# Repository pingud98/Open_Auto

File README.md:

# Open_Auto

Open Auto is an open hardware car sharing hardware platform designed for use by local car-sharing co-operatives and community associations. It originally started out as a Pi Hat, but has now changed into a standalone IOT device based on communications hardware from Particle.

The functionality is simple:
1) GPS tracking, allowing the car to be located at all times and used to update the onboard Real-time Clock (RTC)
2) RFID card access (125kHz or other frequency, requires an external module), with either CAN-bus or relays to open/close the car doors
3) Accelerometer to check driving style (requires an Electron)
4) RTC to allow for power saving (wake up once per minute to check status instead of continuously being on)
5) CAN bus interface for automotive communication
6) Particle Electron/Photon socket for Wi-Fi and/or Cellular connectivity
7) An SD card slot for data logging.
8) An I2C header for whatever else you want to connect.

We're currently working on a software stack for the Electron/Photon that will allow all the basic functions to be accessed via the particle API.

The design also includes a case, which you can make in 3mm acrylic. 

This design is licensed under the CERN Open Hardware License V1.2

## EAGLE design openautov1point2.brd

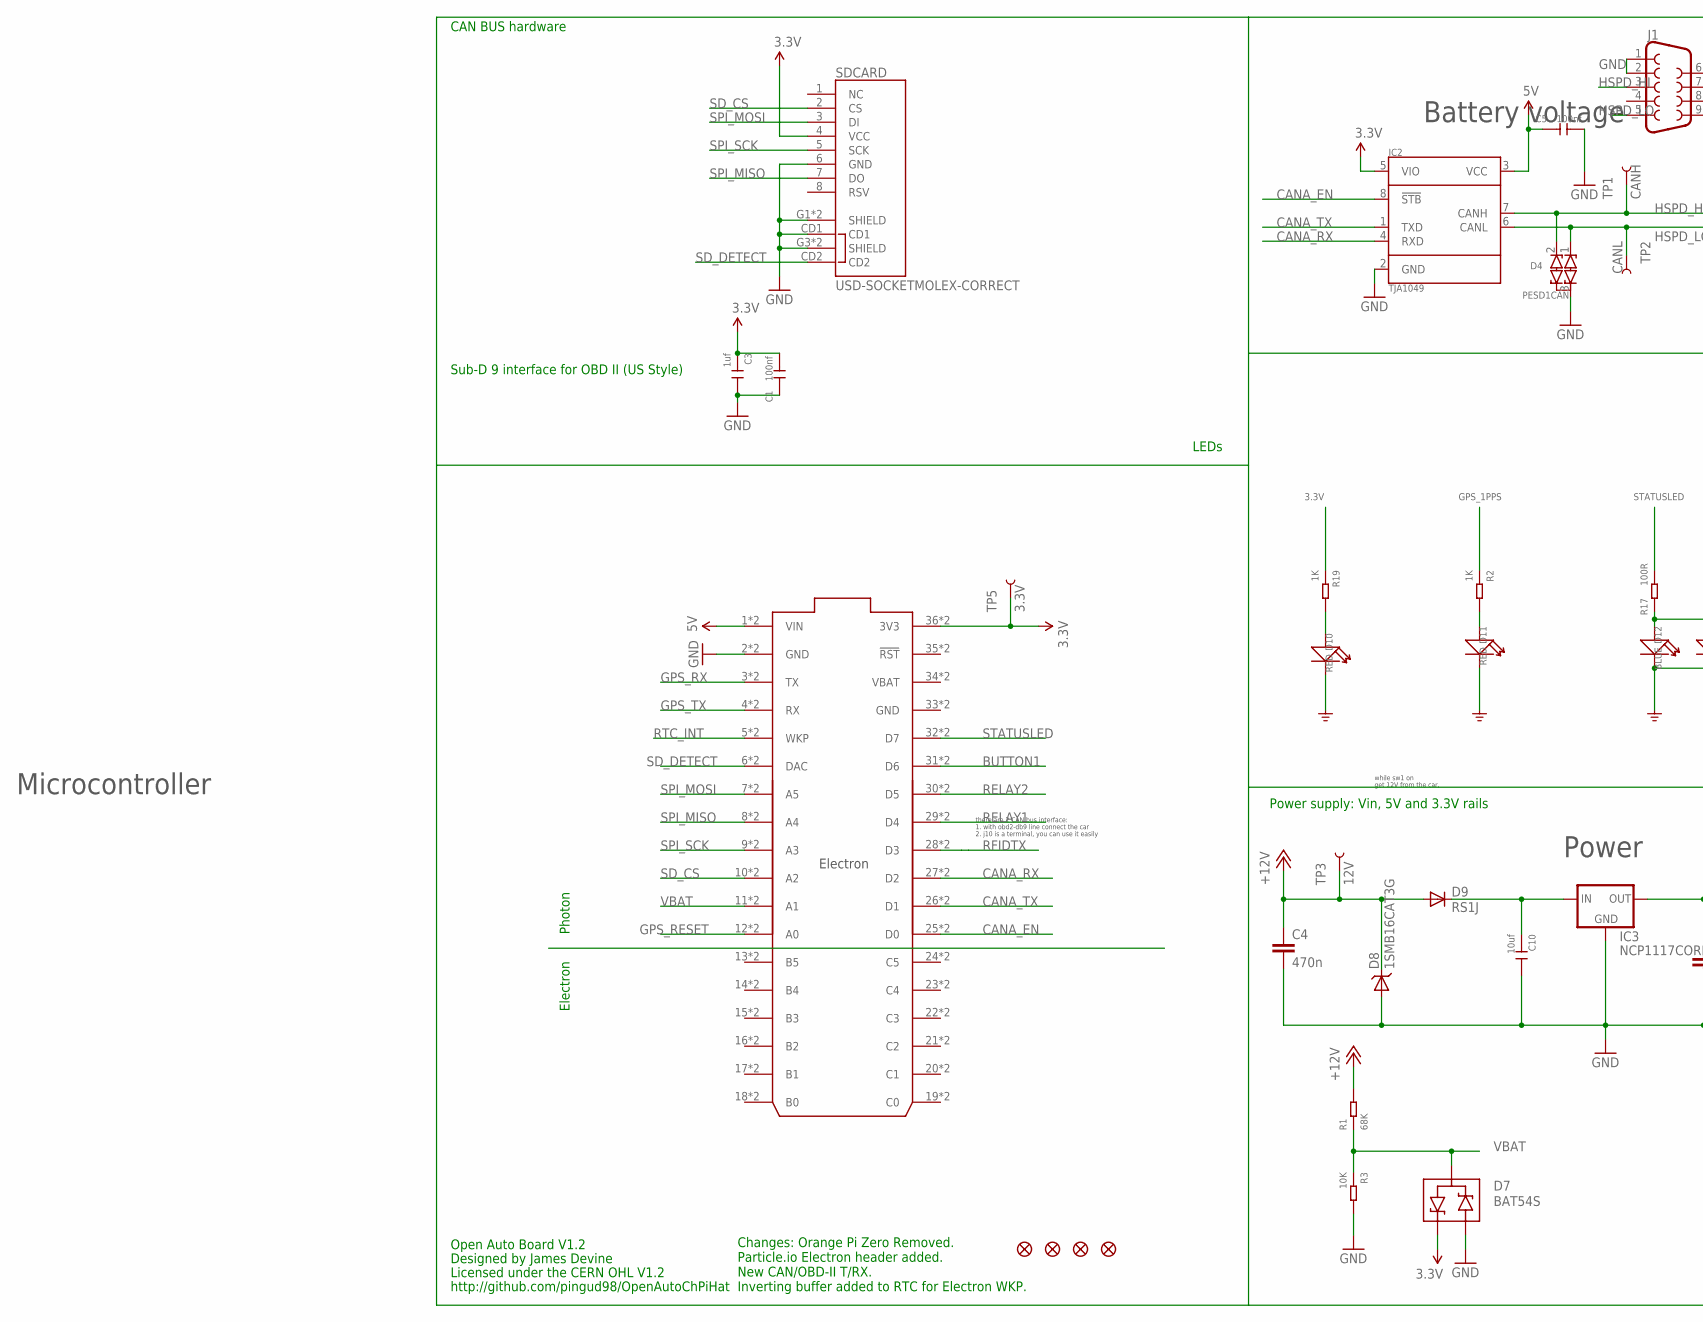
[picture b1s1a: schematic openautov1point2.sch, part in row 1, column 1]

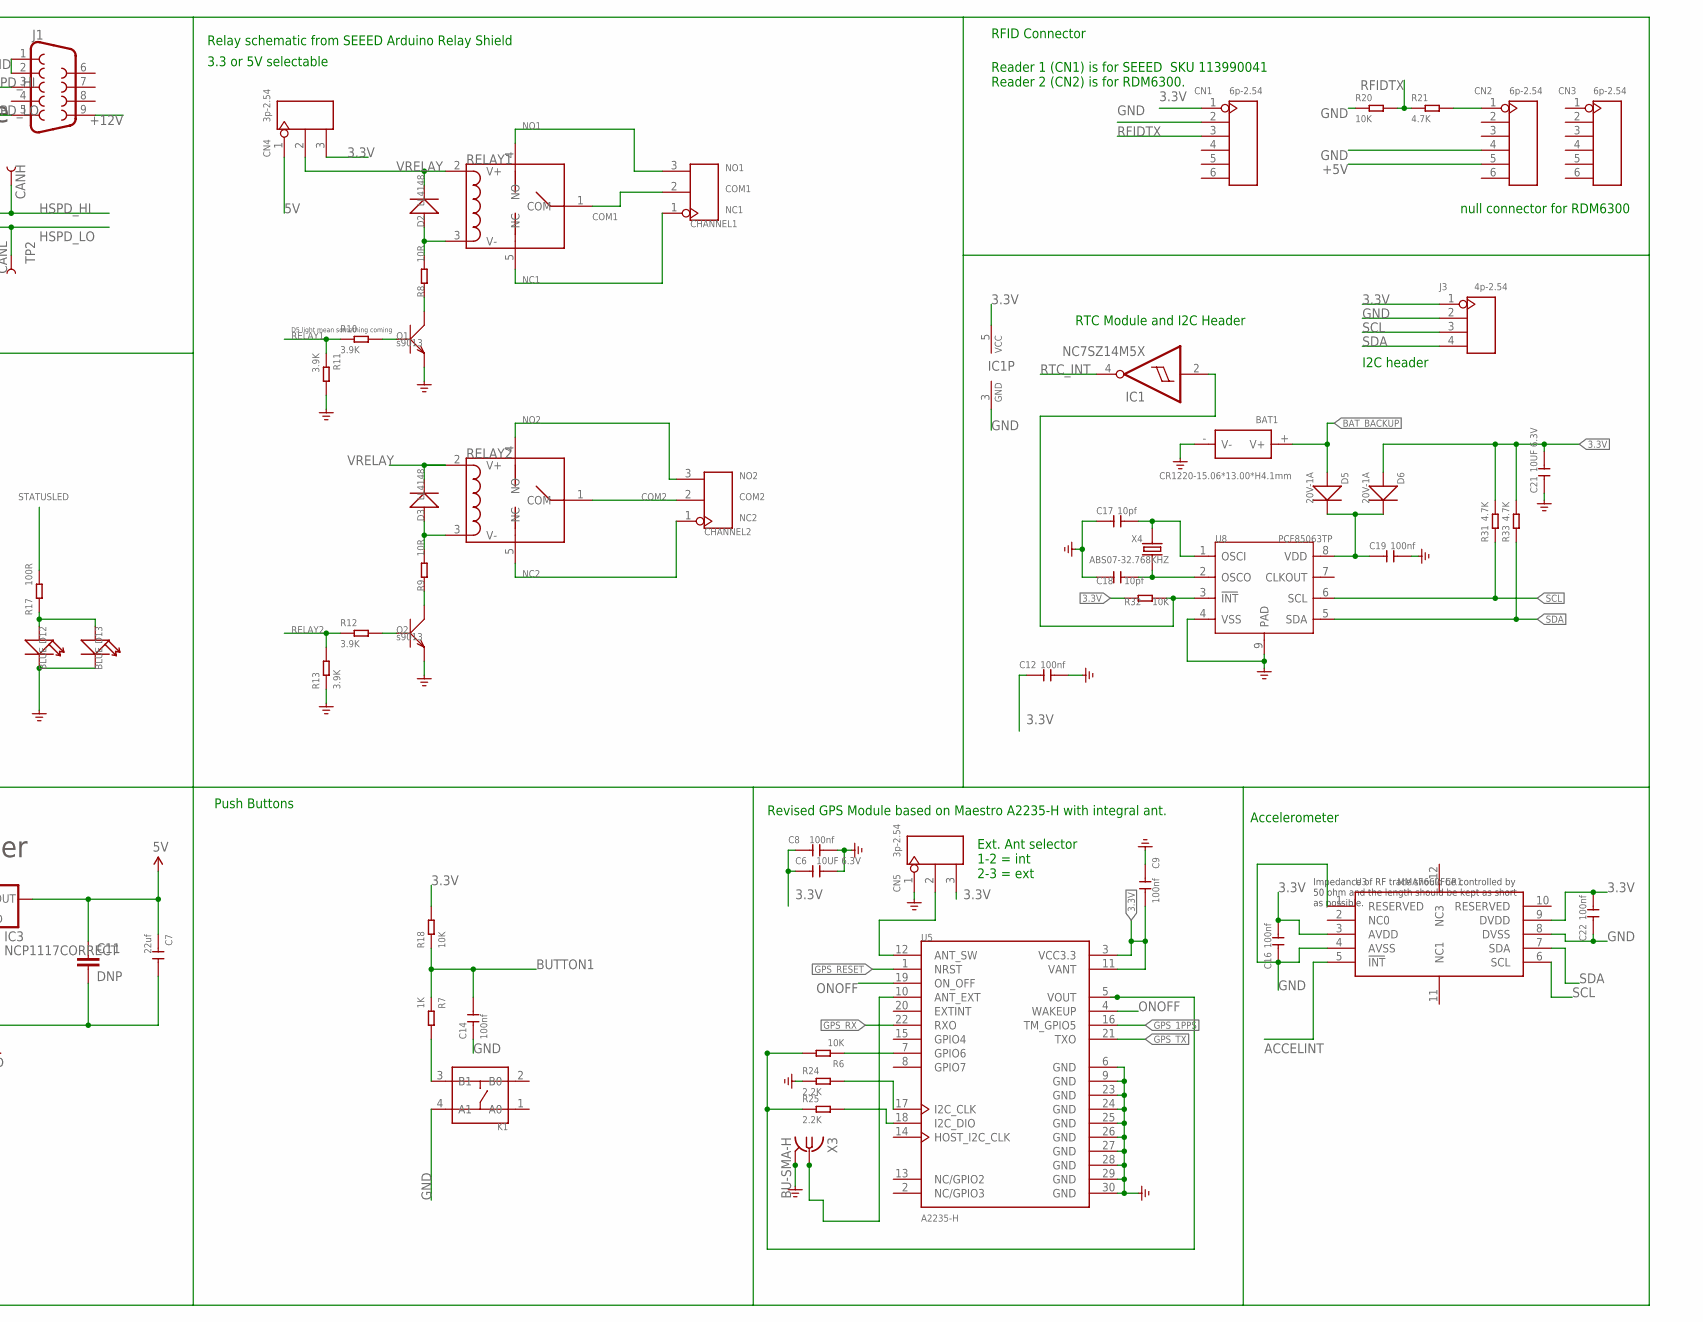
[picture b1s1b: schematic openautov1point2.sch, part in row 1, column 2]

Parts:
BAT1: CR1220-15.06*13.00*H4.1mm; BAT2P-SMD-16.4-CR1220
C1, C5, C8, C9, C12, C14, C16, C19, C22: 100nf; C0603
C3: 1uf; C0603; PARTNO CC0805KKX7R7BB105
C4: 470n; C0805; PARTNO C0805C474K5RACTU
C6, C21: 10UF 6.3V; C0603
C7: 22uf; C0805; PARTNO GRM219R61A226MEA0D
C10: 10uf; C0805; PARTNO GRM21BR6YA106KE43L
C11: DNP; C0805; PARTNO GRM219R61A226MEA0D
C17, C18: 10pf; C0603
CHANNEL1, CHANNEL2: SCREW-TERMINAL-3P'3.5'; 3P-3.5
CN1, CN2, CN3: 6p-2.54; H6-2.54
CN4, CN5: 3p-2.54; H3-2.54
D2, D3: LL4148; LL-34
D4: PESD1CAN; SOT23; PARTNO PESD1CAN-215
D5, D6: 20V-1A; SOD-123
D7: BAT54S; SOT23; PARTNO BAT54S-7-F
D8: 1SMB16CAT3G; SMB-DIODE; PARTNO 1SMB16CAT3G
D9: RS1J; SMA-DIODE; PARTNO RS1J-E3/5AT
D10, D11: RED; LED-0603
D12, D13: BLUE; LED-0603
ELECTRON: ELECTRON_WITH_EXTERNAL_HEADERS; ELECTRON_EXTERNAL; PARTNO PPTC181LFBN-RC
FID1, FID2, FID3, FID4: FIDUCIAL1.5X3; FIDUCIAL-1.5X3
IC1: NC7SZ14M5X; SOT23-5
IC2: TJA1049; SO8; PARTNO TJA1049T-118
IC3: NCP1117CORRECT; SOT223; PARTNO NCP1117LPST50T3G
J1: DB9MALE; DB9_MALE
J3: 4p-2.54; H4-2.54
K1: DIP-SWITCH-TACTILE-SPST-NO/TS-1109(4P-D6.0MM)'TS-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; SW4-6.0X6.0X5.0MM
Q1, Q2: s9013; SOT23
R1: 68K; R0603; PARTNO ERJ-6ENF6202V
R2, R7, R19: 1K; R0603
R3, R6, R18, R20, R32: 10K; R0603
R8, R9: 10R; R0603
R10, R11, R12, R13: 3.9K; R0603
R17: 100R; R0603
R21, R31, R33: 4.7K; R0603
R24, R25: 2.2K; R0603
RELAY1, RELAY2: RELAY-HLS8L-DC5V-S-C; 5P-19.0X15.5X15.8H
SDCARD: USD-SOCKETMOLEX-CORRECT; MICRO-SD-MOLEX-CORRECT; PARTNO 1040310811
TP1: CANH; PAD.03X.03
TP2: CANL; PAD.03X.03
TP3: 12V; PAD.03X.03
TP5: 3.3V; PAD.03X.03
U3: MMA7660FCR1; DFN10-0.5-3.0X3.0MM
U5: A2235-H; XCVR_A2235-H
U8: PCF85063TP; HWSON8-0.5-2X3X0.75MM
X3: BU-SMA-H
X4: ABS07-32.768KHZ; X2-SMD-3.2X1.5X0.55MM

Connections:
3.3V: C1.2, C3.1, C6.1, C8.1, C9.2, C12.1, C16.2, C21.2, C22.2, CN1.1, CN4.3, D6.+, D7.2 (C1), ELECTRON.36 (3V3), ELECTRON.@36 (3V3), IC1.5 (VCC), IC2.5 (VIO), J3.1, R18.2, R19.1, R31.2, R32.1, R33.2, SDCARD.4 (VCC), TP5.P$1, U3.3 (AVDD), U3.9 (DVDD), U5.3 (VCC3.3), U5.11 (VANT)
5V: C5.1, C7.1, C11.1, CN4.1, ELECTRON.1 (VIN), ELECTRON.@1 (VIN), IC2.3 (VCC), IC3.2 (OUT), IC3.4 (OUT)
!RTC_INT: IC1.2 (I), R32.2, U8.3 (!INT)
+5V: CN2.5
+12V: C4.1, D8.C, D9.A, J1.9, R1.2, TP3.P$1
ACCELINT: U3.5 (!INT)
BAT_BACKUP: BAT1.+ (V+), D5.+
BUTTON1: C14.2, ELECTRON.31 (D6), ELECTRON.@31 (D6), R7.1, R18.1
CANA_EN: ELECTRON.25 (D0), ELECTRON.@25 (D0), IC2.8 (!STB)
CANA_RX: ELECTRON.27 (D2), ELECTRON.@27 (D2), IC2.4 (RXD)
CANA_TX: ELECTRON.26 (D1), ELECTRON.@26 (D1), IC2.1 (TXD)
COM1: CHANNEL1.2, RELAY1.1 (COM)
COM2: CHANNEL2.2, RELAY2.1 (COM)
GND: BAT1.- (V-), C1.1, C3.2, C4.2, C5.2, C6.2, C7.2, C8.2, C9.1, C10.2, C11.2, C12.2, C14.1, C16.1, C17.1, C18.1, C19.2, C21.1, C22.1, CN1.2, CN2.4, CN5.1, D4.3 (COM), D7.1 (A2), D8.A, D10.-, D11.-, D12.-, D13.-, ELECTRON.2 (GND), ELECTRON.33 (GND), ELECTRON.@2 (GND), ELECTRON.@33 (GND), IC1.3 (GND), IC2.2 (GND), IC3.1 (GND), J1.1, J1.2, J3.2, K1.4 (A1), Q1.2 (E), Q2.2 (E), R3.2, R11.2, R13.1, R20.1, R24.1, SDCARD.6 (GND), SDCARD.CD1, SDCARD.G1 (SHIELD), SDCARD.G2 (SHIELD), SDCARD.G3 (SHIELD), SDCARD.G4 (SHIELD), U3.1 (RESERVED), U3.4 (AVSS), U3.8 (DVSS), U5.6 (GND), U5.9 (GND), U5.23 (GND), U5.24 (GND), U5.25 (GND), U5.26 (GND), U5.27 (GND), U5.28 (GND), U5.29 (GND), U5.30 (GND), U8.4 (VSS), U8.9 (PAD), X3.2, X3.3 (2), X3.4 (2), X3.5 (2)
GPS_1PPS: R2.1, U5.16 (TM_GPIO5)
GPS_RESET: ELECTRON.12 (A0), ELECTRON.@12 (A0), U5.1 (NRST)
GPS_RX: ELECTRON.3 (TX), ELECTRON.@3 (TX), U5.22 (RXO)
GPS_TX: ELECTRON.4 (RX), ELECTRON.@4 (RX), U5.21 (TXO)
HSPD_HI: D4.2 (C2), IC2.7 (CANH), J1.3, TP1.P$1
HSPD_LO: D4.1 (C1), IC2.6 (CANL), J1.5, TP2.P$1
unnamed: K1.3 (B1), R7.2
unnamed: CN5.2, U5.12 (ANT_SW)
unnamed: Q2.1 (B), R12.2
unnamed: D3.A (+), R9.2, RELAY2.3 (V-)
unnamed: Q1.3 (C), R8.1
unnamed: D2.A (+), R8.2, RELAY1.3 (V-)
unnamed: Q2.3 (C), R9.1
unnamed: D11.+, R2.2
unnamed: D12.+, D13.+, R17.2
unnamed: U5.10 (ANT_EXT), X3.1
unnamed: R6.2, R25.1, U5.5 (VOUT)
unnamed: R6.1, U5.7 (GPIO6)
unnamed: Q1.1 (B), R10.2
unnamed: CN2.1, R21.2
unnamed: R24.2, U5.17 (I2C_CLK)
unnamed: R25.2, U5.18 (I2C_DIO)
unnamed: D10.+, R19.2
unnamed: C18.2, U8.2 (OSCO), X4.1
unnamed: C17.2, U8.1 (OSCI), X4.2
unnamed: C10.1, D9.C, IC3.3 (IN)
unnamed: C19.1, D5.-, D6.-, U8.8 (VDD)
NC1: CHANNEL1.1, RELAY1.5 (NC)
NC2: CHANNEL2.1, RELAY2.5 (NC)
NO1: CHANNEL1.3, RELAY1.4 (NO)
NO2: CHANNEL2.3, RELAY2.4 (NO)
ONOFF: U5.4 (WAKEUP), U5.19 (ON_OFF)
RELAY1: ELECTRON.29 (D4), ELECTRON.@29 (D4), R10.1, R11.1
RELAY2: ELECTRON.30 (D5), ELECTRON.@30 (D5), R12.1, R13.2
RFIDTX: CN1.3, ELECTRON.28 (D3), ELECTRON.@28 (D3), R20.2, R21.1
RTC_INT: ELECTRON.5 (WKP), ELECTRON.@5 (WKP), IC1.4 (O)
SCL: J3.3, R31.1, U3.6 (SCL), U8.6 (SCL)
SDA: J3.4, R33.1, U3.7 (SDA), U8.5 (SDA)
SD_CS: ELECTRON.10 (A2), ELECTRON.@10 (A2), SDCARD.2 (CS)
SD_DETECT: ELECTRON.6 (DAC), ELECTRON.@6 (DAC), SDCARD.CD2
SPI_MISO: ELECTRON.8 (A4), ELECTRON.@8 (A4), SDCARD.7 (DO)
SPI_MOSI: ELECTRON.7 (A5), ELECTRON.@7 (A5), SDCARD.3 (DI)
SPI_SCK: ELECTRON.9 (A3), ELECTRON.@9 (A3), SDCARD.5 (SCK)
STATUSLED: ELECTRON.32 (D7), ELECTRON.@32 (D7), R17.1
VBAT: D7.3 (COM), ELECTRON.11 (A1), ELECTRON.34 (VBAT), ELECTRON.@11 (A1), ELECTRON.@34 (VBAT), R1.1, R3.1
VRELAY: CN4.2, D2.C (-), D3.C (-), RELAY1.2 (V+), RELAY2.2 (V+)

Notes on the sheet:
D5 light mean something coming
CAN BUS hardware
there are 2 CAN bus interface:
1. with obd2-db9 line connect the car
2. j10 is a terminal, you can use it easily
Sub-D 9 interface for OBD II (US Style)
get 12V from the car,
while sw1 on
Relay schematic from SEEED Arduino Relay Shield
RFID Connector
Reader 1 (CN1) is for SEEED SKU 113990041 Reader 2 (CN2) is for RDM6300.
RTC Module and I2C Header
Impedance of RF trace should be controlled by 50 ohm and the length should be kept as short as possible.
Revised GPS Module based on Maestro A2235-H with integral ant.
LEDs
Open Auto Board V1.2
Designed by James Devine
Licensed under the CERN OHL V1.2
http://github.com/pingud98/OpenAutoChPiHat
Changes: Orange Pi Zero Removed. Particle.io Electron header added. New CAN/OBD-II T/RX. Inverting buffer added to RTC for Electron WKP.
Push Buttons
Accelerometer
Power supply: Vin, 5V and 3.3V rails
null connector for RDM6300
I2C header
Battery voltage
Microcontroller
Power
Photon
Electron
3.3 or 5V selectable
Ext. Ant selector 1-2 = int 2-3 = ext

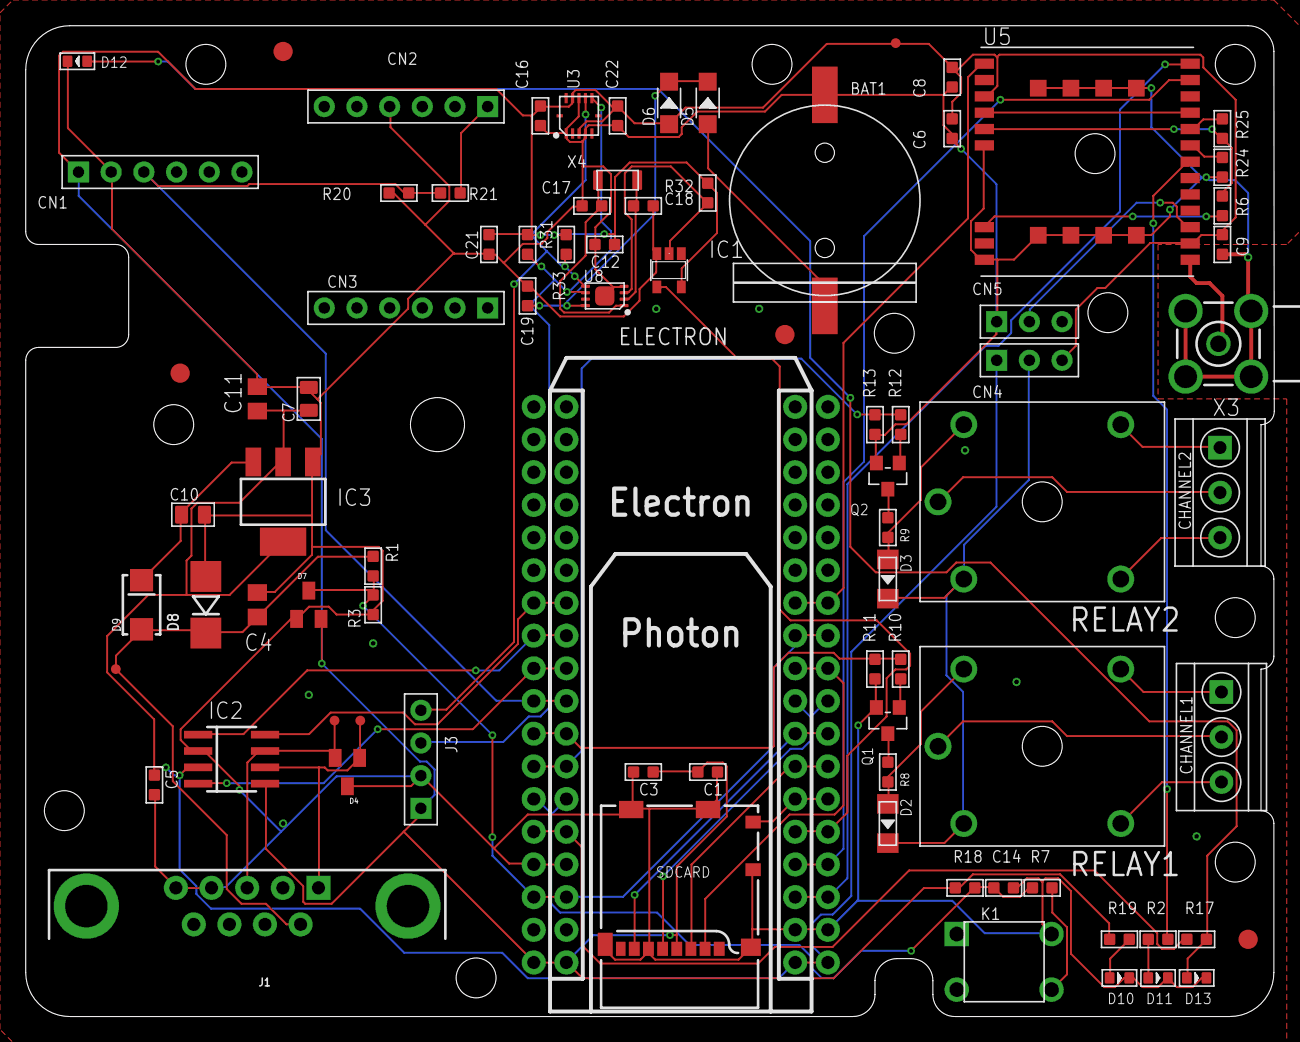
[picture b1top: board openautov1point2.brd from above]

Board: 2 copper layers, 97.0 x 77.0 mm, 84 parts (0 on the bottom side), 58 nets.

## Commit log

2017-12-11 Forking the openauto pi hat already
    New version based on the Particle.io Photon and Electron.
    Decided to ditch the name hat, since it isn't a hat anymore!
2017-12-13 updated after design review
2017-12-22 RDM6300 footprint corrected
2017-12-24 Final update before Production, BOM still needs tidying
2017-12-25 Production versions
2017-12-30 A 3mm laser cut acrylic case
2017-12-30 tidyup complete
2017-12-30 added fiducials to PCB, created case
2018-01-22 corrected parts for Ch1/2, X4 and C5
2018-01-22 Added laser cut case, .brd + .dxf + annotated pdf
2018-03-04 Added real information.

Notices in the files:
parts and their libraries:
SparkFun-Connectors: Licensing: Creative Commons ShareAlike 4.0 International - https://creativecommons.org/licenses/by-sa/4.0
SparkFun-Aesthetics: Licensing: CC v3.0 Share-Alike You are welcome to use this library for commercial purposes.
